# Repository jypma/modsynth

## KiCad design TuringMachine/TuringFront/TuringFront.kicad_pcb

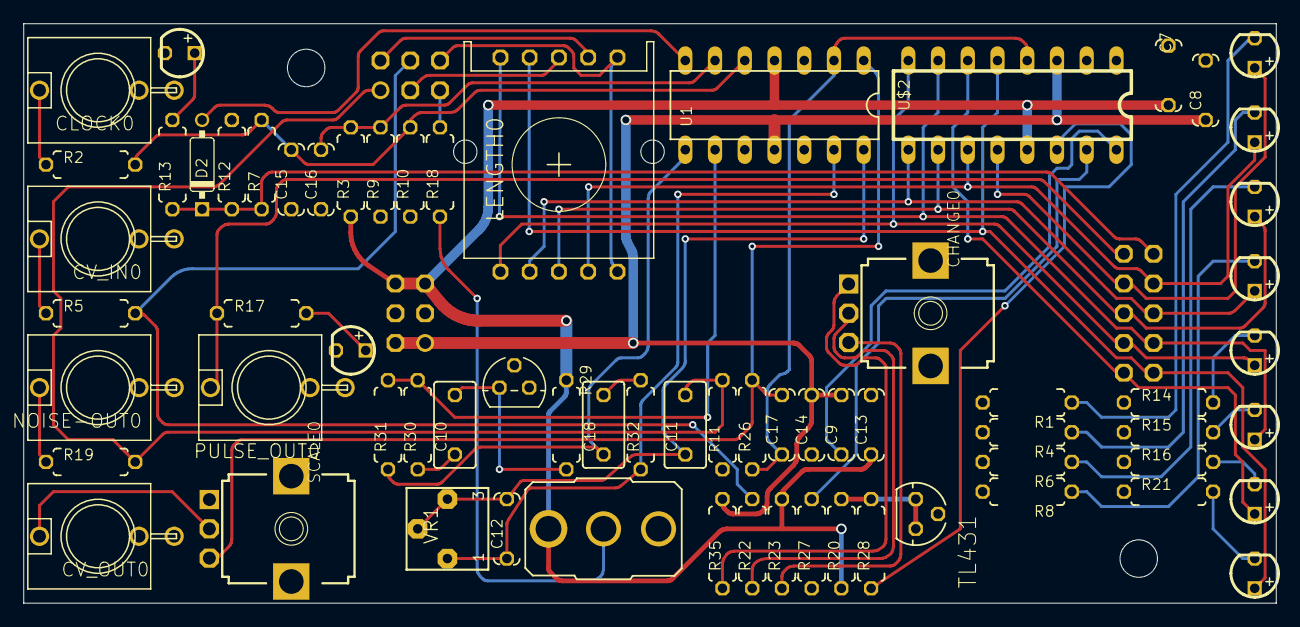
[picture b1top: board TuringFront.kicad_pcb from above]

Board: 4 copper layers, 107.0 x 49.5 mm, 73 parts (0 on the bottom side), 53 nets.

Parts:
C7, C8, C13, C14, C16: 100n; C050-024X044
C9: 10n; C050-024X044
C10, C11, C18: 0.47uf; C050-035X075
C12, C17: 1n; C050-024X044
C15: 330pf; C050-024X044
CHANGE0: 50k; 9MM_SNAP-IN_POT
CLK0: LED3MM
CLOCK0: THONKICONNNEW; WQP-PJ301M-12_JACK
CV_IN0: THONKICONNNEW; WQP-PJ301M-12_JACK
CV_OUT0: THONKICONNNEW; WQP-PJ301M-12_JACK
D2: 1N4148; DO35-7
LENGTH0: ALPS-SRBV
LINK1, LINK2: MA03-2BACKSIDE
LINK3: 10PIN_BACKSIDE
NOISE-OUT0: THONKICONNNEW; WQP-PJ301M-12_JACK
PULS1: LED3MM
PULSE_OUT0: THONKICONNNEW; WQP-PJ301M-12_JACK
R1, R4, R6, R8, R13, R14, R15, R16, R17, R21: 2.2k; 0207_7
R2, R9: 15k; 0207_7
R3: 68k; 0207_7
R5: 51k; 0207_7
R7, R31: 470k; 0207_7
R10, R22, R29: 100k; 0207_7
R11: 100k; 7MM_RESISTOR
R12, R23, R30, R35: 10k; 0207_7
R18, R19, R32: 1k; 0207_7
R20: 3.3k; 0207_7
R26: 5.1k; 0207_7
R27, R28: 1.6k; 0207_7
SCALE0: 50k; 9MM_SNAP-IN_POT
T1: 2N3904; TO92
TL431: TO92-CLP
U1: TL074_; DIL14
U$2: DAC0800; DIL16
U$4, U$5: MOUNTING_HOLE
UNK1, UNK2, UNK3, UNK4, UNK5, UNK6, UNK7, UNK8: LED3MM
VR1: 1m; BOURNS_3362P_TRIMMER
WRITE0: T-80-T-SPDT-ON-OFF-ON; M9040P

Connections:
+12V_FRONT: C7.2, C13.1, LINK2.5, LINK2.6, R3.1, R20.1, R23.2, R29.1, U1.4, U$2.13, WRITE0.1
-12V_FRONT: C8.1, C9.2, C14.2, LINK2.1, LINK2.2, R35.2, U1.11, U$2.3
B1_FRONT: LENGTH0.F, LINK3.1, U$2.5, UNK1.A
B2_FRONT: LINK3.2, U$2.6, UNK2.A
B3_FRONT: LENGTH0.E, LINK3.3, U$2.7, UNK3.A
B4_FRONT: LENGTH0.D, LINK3.4, U$2.8, UNK4.A
B5_FRONT: LENGTH0.C, LINK3.5, U$2.9, UNK5.A
B6_FRONT: LENGTH0.B, LINK3.6, U$2.10, UNK6.A
B7_FRONT: LENGTH0.A, LINK3.7, U$2.11, UNK7.A
B8_FRONT: LINK3.8, U$2.12, UNK8.A
CLOCK_FRONT: D2.C, LINK3.9, R7.1, R12.1, R13.1
END_OF_LOOP_FRONT: LENGTH0.COM, LENGTH0.COM2, LINK1.6
GND_FRONT: C7.1, C8.2, C13.2, C14.1, C15.1, C16.1, CHANGE0.CHASSIS2, CLK0.K, CLOCK0.P$3_SLEEVE, CV_IN0.P$3_SLEEVE, CV_OUT0.P$3_SLEEVE, LINK2.3, LINK2.4, NOISE-OUT0.P$3_SLEEVE, PULS1.K, PULSE_OUT0.P$3_SLEEVE, R1.2, R4.2, R6.2, R8.2, R9.1, R10.1, R11.1, R12.2, R14.1, R15.1, R16.1, R21.1, R27.1, SCALE0.1, SCALE0.CHASSIS2, T1.2, TL431.A, U1.3, U1.10, U1.12, U$2.1, U$2.2, WRITE0.3
LOOP_CTRL_FRONT: LINK1.4, R5.2, R22.2
MAIN_OUT: C17.2, R26.2, SCALE0.3, U1.1
unnamed: CLOCK0.P$1_TIP, R2.1
unnamed: CV_IN0.P$1_TIP, R5.1
unnamed: C15.2, R2.2, R7.2, R10.2, U1.5
unnamed: PULS1.A, R17.2
unnamed: D2.A, U1.7
unnamed: C18.2, R32.2
unnamed: R18.1, WRITE0.2
unnamed: C16.2, R3.2, R9.2, U1.6
unnamed: C17.1, R26.1, U1.2, U$2.4
unnamed: CLK0.A, R13.2
unnamed: C10.2, R29.2, T1.3
unnamed: R20.2, R28.2, TL431.C, TL431.R
unnamed: C10.1, R30.1
unnamed: R30.2, R31.2, U1.9
unnamed: C18.1, R31.1, U1.8
unnamed: R27.2, U$2.15
unnamed: C9.1, U$2.16
unnamed: R28.1, U$2.14
unnamed: C12.1, R32.1, U1.13, VR1.1
unnamed: R1.1, UNK8.K
unnamed: R4.1, UNK7.K
unnamed: R6.1, UNK6.K
unnamed: R8.1, UNK5.K
unnamed: R14.2, UNK4.K
unnamed: R15.2, UNK3.K
unnamed: R16.2, UNK2.K
unnamed: R21.2, UNK1.K
unnamed: CV_OUT0.P$1_TIP, SCALE0.2
unnamed: NOISE-OUT0.P$1_TIP, R19.1
unnamed: C11.1, C12.2, U1.14, VR1.2, VR1.3
unnamed: CHANGE0.2, R22.1
unnamed: CHANGE0.3, R23.1
unnamed: CHANGE0.1, R35.1
NOISE_FRONT: C11.2, LINK1.1, R11.2, R19.2
PULSE_OUT_FRONT: LINK3.10, PULSE_OUT0.P$1_TIP, R17.1
STEP_12_FRONT: LENGTH0.G, LINK1.3
STEP_16_FRONT: LENGTH0.H, LINK1.2
WRITE_SW_FRONT: LINK1.5, R18.2

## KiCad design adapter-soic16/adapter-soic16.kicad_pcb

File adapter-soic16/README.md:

#  SOIC-16 to DIP-16 adapter

A simple adapter board that allows you to mount an SOIC-16 in a DIP-16 socket. One side uses SMD headers, so the other side can have a SOIC-16 footprint.

This was designed since some TuringMachine parts turned out to only be available in SOIC, while the boards were already manufactured with DIP sockets.

### Schematic

### PCB

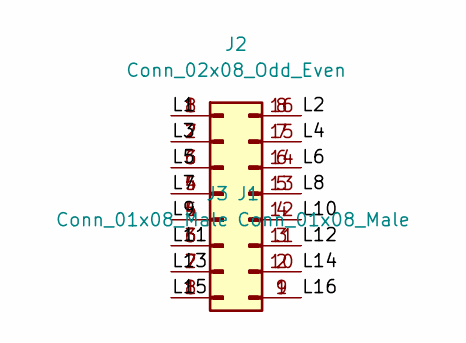
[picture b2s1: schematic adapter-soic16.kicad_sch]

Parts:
J1: Conn_01x08_Male; PinHeader_1x08_P2.54mm_Vertical_SMD_Pin1Left
J2: Conn_02x08_Odd_Even; SOIC-16_3.9x9.9mm_P1.27mm
J3: Conn_01x08_Male; PinHeader_1x08_P2.54mm_Vertical_SMD_Pin1Right

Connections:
/L1: J1.8, J2.1
/L2: J2.16, J3.8
/L3: J1.7, J2.2
/L4: J2.15, J3.7
/L5: J1.6, J2.3
/L6: J2.14, J3.6
/L7: J1.5, J2.4
/L8: J2.13, J3.5
/L9: J1.4, J2.5
/L10: J2.12, J3.4
/L11: J1.3, J2.6
/L12: J2.11, J3.3
/L13: J1.2, J2.7
/L14: J2.10, J3.2
/L15: J1.1, J2.8
/L16: J2.9, J3.1

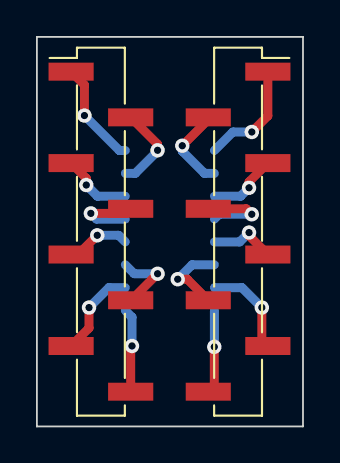
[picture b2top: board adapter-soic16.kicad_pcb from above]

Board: 2 copper layers, 14.8 x 21.6 mm, 3 parts (1 on the bottom side), 16 nets.

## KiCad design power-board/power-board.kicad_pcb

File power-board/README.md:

# Power distribution board

A simple power distribution board with 6 16-pin IDC connectors and a 4-way screw terminal. Silk screen contains markers for 10-pin IDC connectors as well, for modules not using the +5V (none in this repository do).

### Schematic

### PCB

# TODO

- Mounting holes are missing!

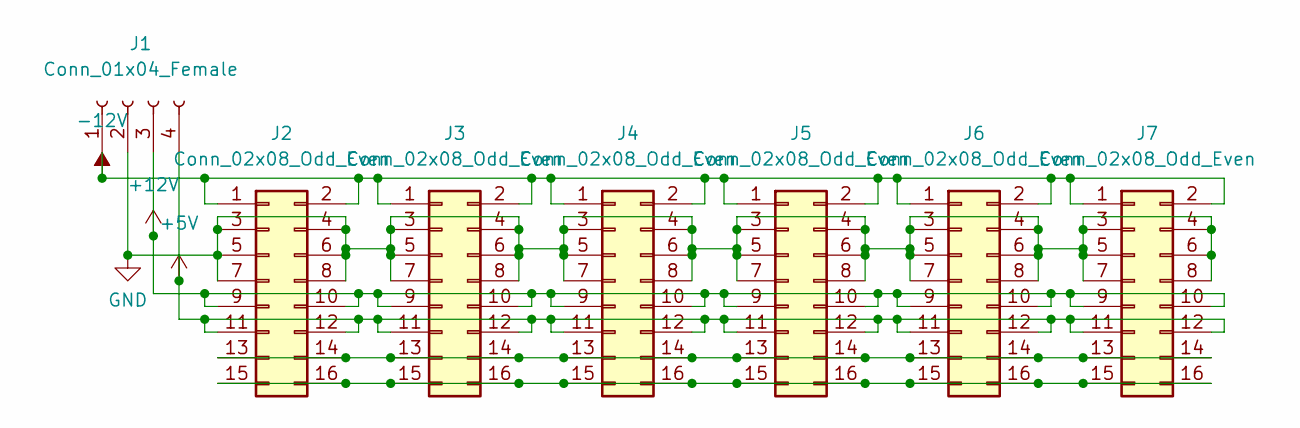
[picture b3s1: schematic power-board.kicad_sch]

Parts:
J1: Conn_01x04_Female; TerminalBlock_MetzConnect_Type055_RT01504HDWU_1x04_P5.00mm_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
J2, J3, J4, J5, J6, J7: Conn_02x08_Odd_Even; IDC-Header_2x08_P2.54mm_Vertical

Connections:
+5V: J1.4, J2.11, J2.12, J3.11, J3.12, J4.11, J4.12, J5.11, J5.12, J6.11, J6.12, J7.11, J7.12
+12V: J1.3, J2.9, J2.10, J3.9, J3.10, J4.9, J4.10, J5.9, J5.10, J6.9, J6.10, J7.9, J7.10
-12V: J1.1, J2.1, J2.2, J3.1, J3.2, J4.1, J4.2, J5.1, J5.2, J6.1, J6.2, J7.1, J7.2
GND: J1.2, J2.3, J2.4, J2.5, J2.6, J2.7, J2.8, J3.3, J3.4, J3.5, J3.6, J3.7, J3.8, J4.3, J4.4, J4.5, J4.6, J4.7, J4.8, J5.3, J5.4, J5.5, J5.6, J5.7, J5.8, J6.3, J6.4, J6.5, J6.6, J6.7, J6.8, J7.3, J7.4, J7.5, J7.6, J7.7, J7.8
unnamed: J2.13, J2.14, J3.13, J3.14, J4.13, J4.14, J5.13, J5.14, J6.13, J6.14, J7.13, J7.14
unnamed: J2.15, J2.16, J3.15, J3.16, J4.15, J4.16, J5.15, J5.16, J6.15, J6.16, J7.15, J7.16

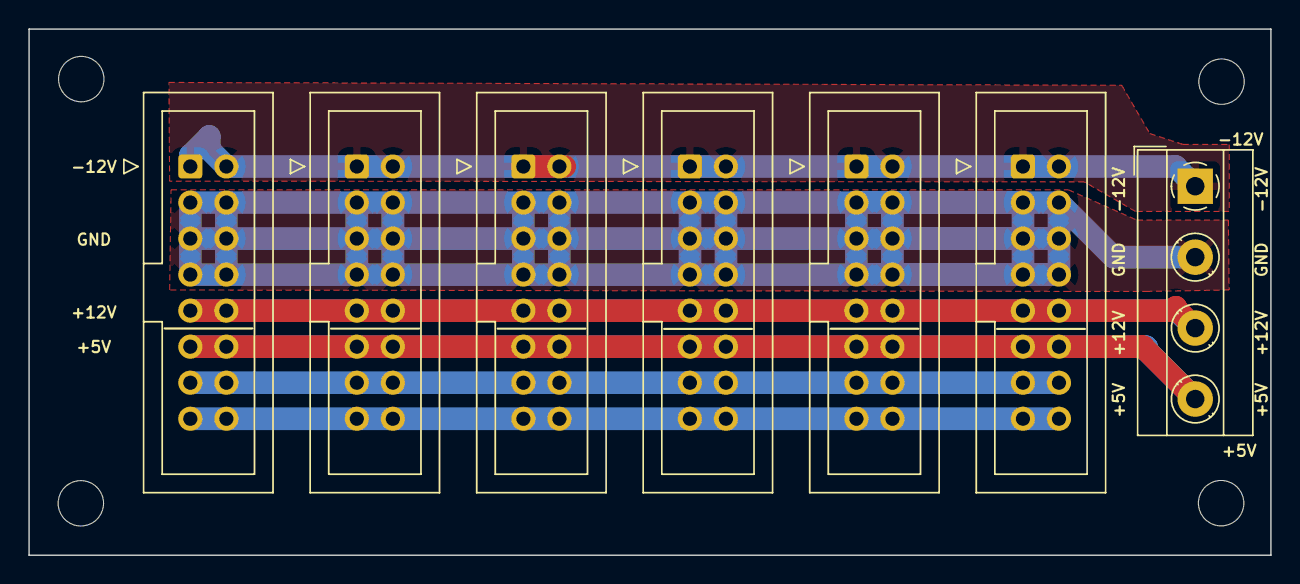
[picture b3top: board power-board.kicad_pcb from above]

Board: 2 copper layers, 87.5 x 37.1 mm, 7 parts (0 on the bottom side), 6 nets.

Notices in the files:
TuringMachine/TuringFront/TuringFront.kicad_pcb:
February 2016 CC-BY-SA
